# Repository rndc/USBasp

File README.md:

# USBasp
USBasp Schematic &amp; PCB layout based on [Thomas Fischl](http://www.fischl.de/usbasp/) design using SMD parts.

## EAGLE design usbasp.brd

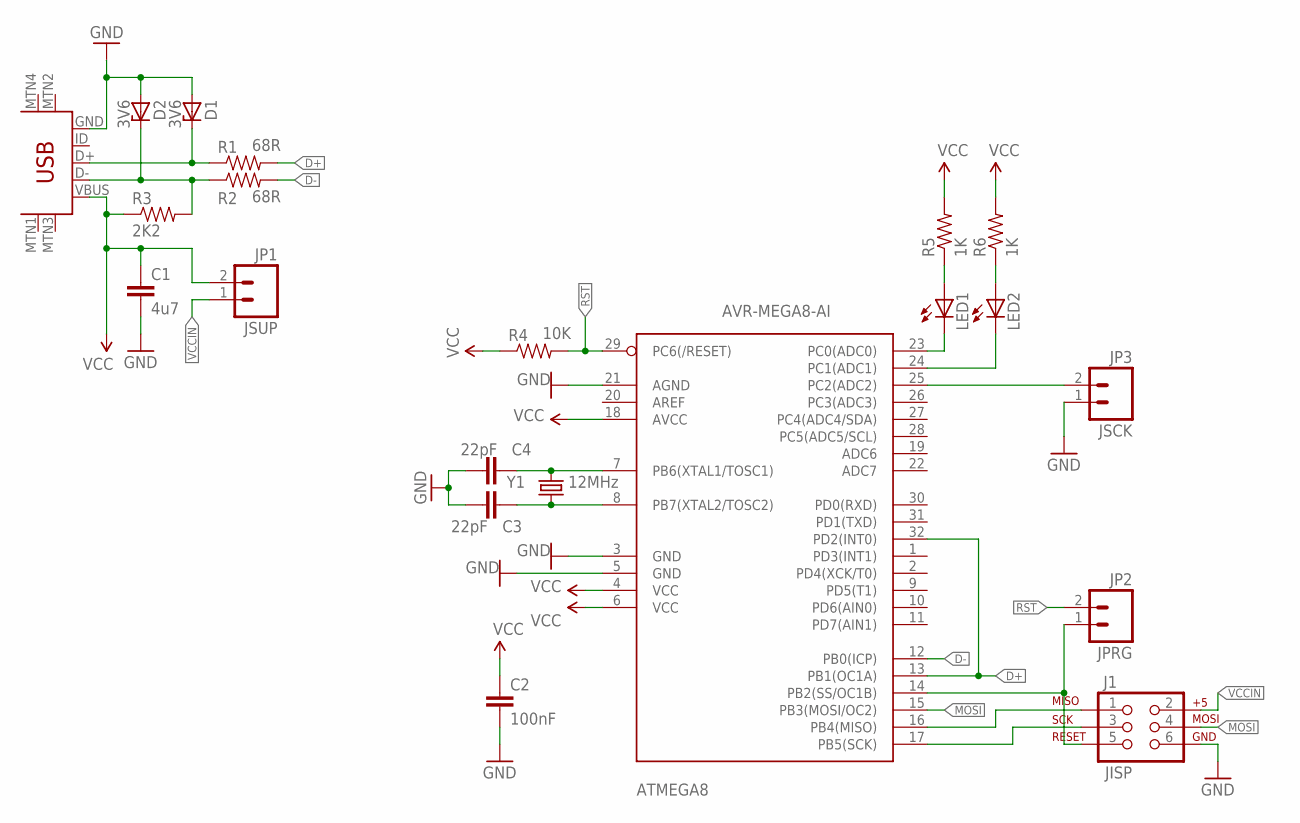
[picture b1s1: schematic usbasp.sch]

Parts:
ATMEGA8: AVR-MEGA8-AI; TQFP32-08
C1: 4u7; 0603-CAP
C2: 100nF; 0805
C3, C4: 22pF; 0805
D1, D2: 3V6; SOD80C
J1: JISP; 2X3
JP1: JSUP; 1X02
JP2: JPRG; 1X02
JP3: JSCK; 1X02
LED1, LED2: LEDCHIPLED_0805; CHIPLED_0805
R1, R2: 68R; 0603-RES
R3: 2K2; 0603-RES
R4: 10K; 0603-RES
R5, R6: 1K; 0603-RES
U$2: USB-MINIB-5PIN; USB-MINIB
Y1: 12MHz; HC49UP

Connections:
D+: ATMEGA8.13 (PB1(OC1A)), ATMEGA8.32 (PD2(INT0)), R1.2
D-: ATMEGA8.12 (PB0(ICP)), R2.2
GND: ATMEGA8.3 (GND), ATMEGA8.5 (GND), ATMEGA8.21 (AGND), C1.2, C2.2, C3.2, C4.1, D1.A, D2.A, J1.6, JP3.1, U$2.GND
MOSI: ATMEGA8.15 (PB3(MOSI/OC2)), J1.4
unnamed: D2.C, R2.1, R3.2, U$2.D-
unnamed: D1.C, R1.1, U$2.D+
unnamed: ATMEGA8.7 (PB6(XTAL1/TOSC1)), C4.2, Y1.1
unnamed: ATMEGA8.8 (PB7(XTAL2/TOSC2)), C3.1, Y1.2
unnamed: ATMEGA8.14 (PB2(SS/OC1B)), J1.5, JP2.1
unnamed: ATMEGA8.23 (PC0(ADC0)), LED1.C
unnamed: ATMEGA8.24 (PC1(ADC1)), LED2.C
unnamed: LED1.A, R5.1
unnamed: LED2.A, R6.1
unnamed: ATMEGA8.25 (PC2(ADC2)), JP3.2
unnamed: ATMEGA8.16 (PB4(MISO)), J1.1
unnamed: ATMEGA8.17 (PB5(SCK)), J1.3
RST: ATMEGA8.29 (PC6(/RESET)), JP2.2, R4.2
VCC: ATMEGA8.4 (VCC), ATMEGA8.6 (VCC), ATMEGA8.18 (AVCC), C1.1, C2.1, JP1.2, R3.1, R4.1, R5.2, R6.2, U$2.VBUS
VCCIN: J1.2, JP1.1

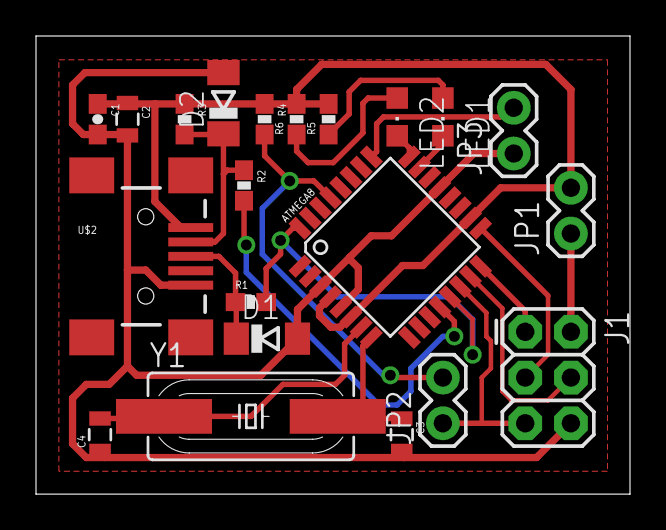
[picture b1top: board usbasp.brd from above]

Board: 2 copper layers, 33.0 x 25.5 mm, 21 parts (0 on the bottom side), 19 nets.

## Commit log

2015-01-20 Make the board a bit smaller
2015-03-15 Added URL to Thomas Fischl's website

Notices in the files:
parts and their libraries:
SparkFun-DigitalIC: Licensing: Creative Commons ShareAlike 4.0 International - https://creativecommons.org/licenses/by-sa/4.0
